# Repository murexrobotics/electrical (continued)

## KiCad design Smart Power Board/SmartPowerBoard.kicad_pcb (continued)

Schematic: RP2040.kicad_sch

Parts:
C11, C12, C13, C15, C16, C36, C37, C38, C39, C40: 0.1uF; C_0402_1005Metric
C14, C35: 1uF; C_0402_1005Metric
C33, C34: 10pF; C_0402_1005Metric
J2: USB_C_Receptacle_USB2.0_16P; USB_C_Receptacle_GCT_USB4105-xx-A_16P_TopMnt_Horizontal
R10, R11: 5.1k; R_0402_1005Metric
R19: 50; R_0402_1005Metric
R20, R21, R34, R35, R37, R38, R39: 10k; R_0402_1005Metric
R40, R41: 27; R_0402_1005Metric
SW1, SW2: SW_Push; SW_Push_SPST_NO_Alps_SKRK
U6: RP2040; QFN-56-1EP_7x7mm_P0.4mm_EP3.2x3.2mm_ThermalVias
U7: W25Q32JVSS; SOIC-8_5.23x5.23mm_P1.27mm
Y1: FL1200138; XTAL_FL1200138; PARTREV N/A

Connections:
/Buck Converter 3.3V/EN: U6.4 (GPIO2); also elsewhere on the board
/Buck Converter 5V/5V_{OUT}: J2.A4 (VBUS), J2.A9 (VBUS), J2.B4 (VBUS), J2.B9 (VBUS); also elsewhere on the board
/Buck Converter 5V/EN: U6.5 (GPIO3); also elsewhere on the board
/MCU/1.1V: C11.2, C12.2, U6.23 (DVDD), U6.45 (VREG_VOUT), U6.50 (DVDD); also elsewhere on the board
/MCU/3.3V_{CC}: C13.2, C14.2, C15.2, C16.2, C35.2, C36.2, C37.2, C38.2, C39.2, C40.2, R21.2, R34.1, R35.1, R37.1, R38.1, R39.1, U6.1 (IOVDD), U6.10 (IOVDD), U6.22 (IOVDD), U6.33 (IOVDD), U6.42 (IOVDD), U6.43 (ADC_AVDD), U6.44 (VREG_IN), U6.48 (USB_VDD), U6.49 (IOVDD), U7.8 (VCC); also elsewhere on the board
/MCU/CRIT: R34.2, U6.16 (GPIO13); also elsewhere on the board
/MCU/GPIO15: U6.18 (GPIO15); also elsewhere on the board
/MCU/QSPI_CS: R20.2, R21.1, U6.56 (QSPI_SS), U7.1 (~CS)
/MCU/QSPI_SCLK: U6.52 (QSPI_SCLK), U7.6 (CLK)
/MCU/QSPI_SD0: U6.53 (QSPI_SD0), U7.5 (DI(IO0))
/MCU/QSPI_SD1: U6.55 (QSPI_SD1), U7.2 (DO(IO1))
/MCU/QSPI_SD2: U6.54 (QSPI_SD2), U7.3 (IO2)
/MCU/QSPI_SD3: U6.51 (QSPI_SD3), U7.7 (IO3)
/MCU/RUN: R39.2, SW1.1, U6.26 (RUN)
/MCU/SCL: R37.2, U6.2 (GPIO0); also elsewhere on the board
/MCU/SDA: R38.2, U6.3 (GPIO1); also elsewhere on the board
/MCU/USB_BOOT: R20.1, SW2.1
/MCU/USB_M: J2.A6 (D+), J2.B6 (D+), R41.1
/MCU/USB_P: J2.A7 (D-), J2.B7 (D-), R40.1
/MCU/WARN: R35.2, U6.17 (GPIO14); also elsewhere on the board
/MCU/XIN: C34.1, U6.20 (XIN), Y1.1
/MCU/XOUT: R19.2, U6.21 (XOUT)
GND: C11.1, C12.1, C13.1, C14.1, C15.1, C16.1, C33.2, C34.2, C35.1, C36.1, C37.1, C38.1, C39.1, C40.1, J2.A1 (GND), J2.A12 (GND), J2.B1 (GND), J2.B12 (GND), J2.S1 (SHIELD), R10.2, R11.1, SW1.2, SW2.2, U6.19 (TESTEN), U6.57 (GND), U7.4 (GND), Y1.2 (GND), Y1.4 (GND__1); also elsewhere on the board
unnamed: C33.1, R19.1, Y1.3
unnamed: J2.A5 (CC1), R10.1
unnamed: J2.B5 (CC2), R11.2
unnamed: R41.2, U6.46 (USB_DM)
unnamed: R40.2, U6.47 (USB_DP)

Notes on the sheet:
RESET Button
USB_BOOT Button
USB Connection
Decoupling Capacitors
Clock
Flash Memory
RP2040 Main

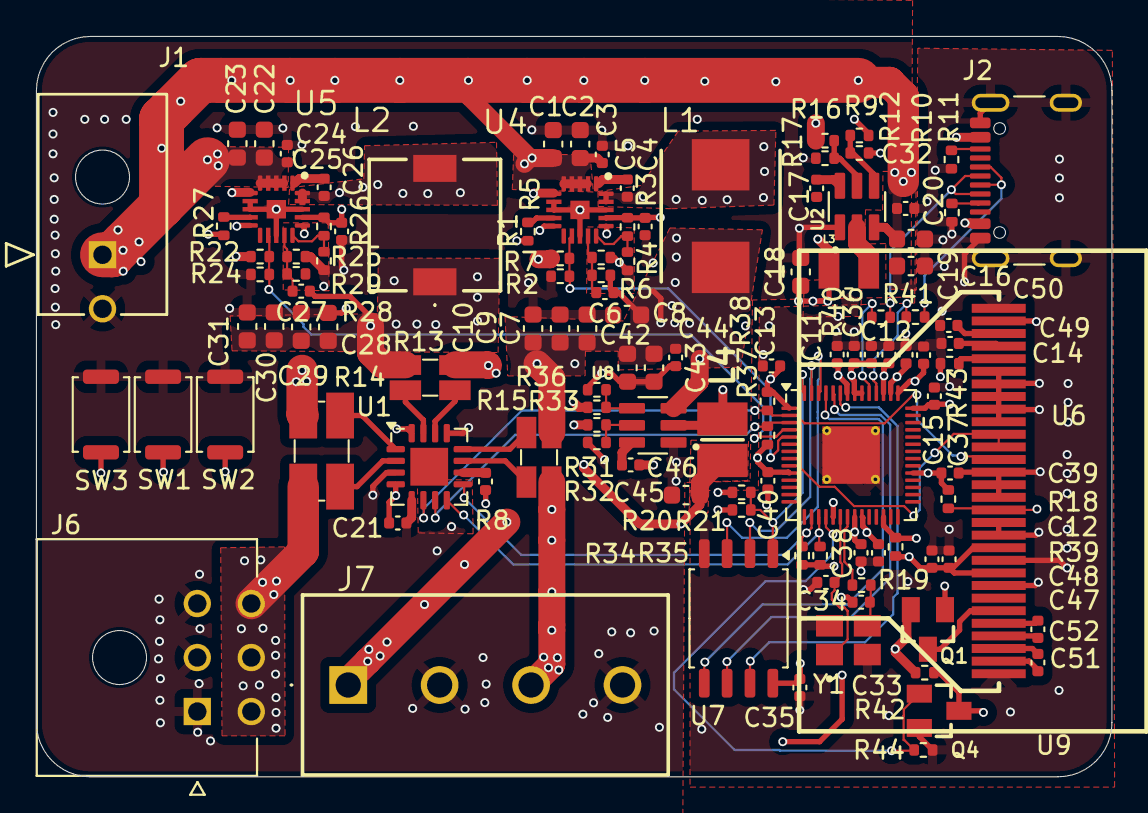
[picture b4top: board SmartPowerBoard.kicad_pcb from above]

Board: 4 copper layers, 59.8 x 41.1 mm, 116 parts (0 on the bottom side), 71 nets.

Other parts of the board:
C12#2: 0.1uF; C_0402_1005Metric

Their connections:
/MCU/1.1V: C12#2.2; also elsewhere on the board
GND: C12#2.1; also elsewhere on the board

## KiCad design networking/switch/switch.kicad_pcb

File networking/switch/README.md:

# Documentation

<https://docs.murexrobotics.com/elec/boards/networking/switch>

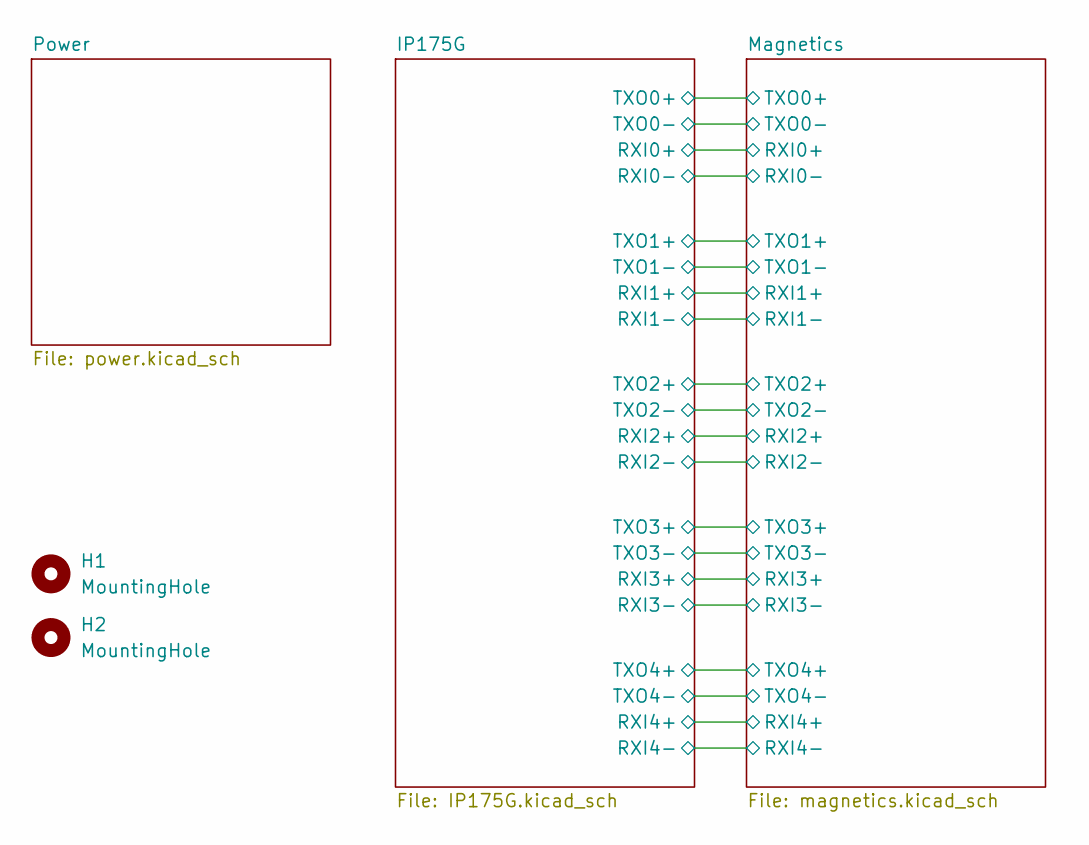
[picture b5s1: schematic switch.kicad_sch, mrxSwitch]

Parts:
H1, H2: MountingHole; MountingHole_3.2mm_M3

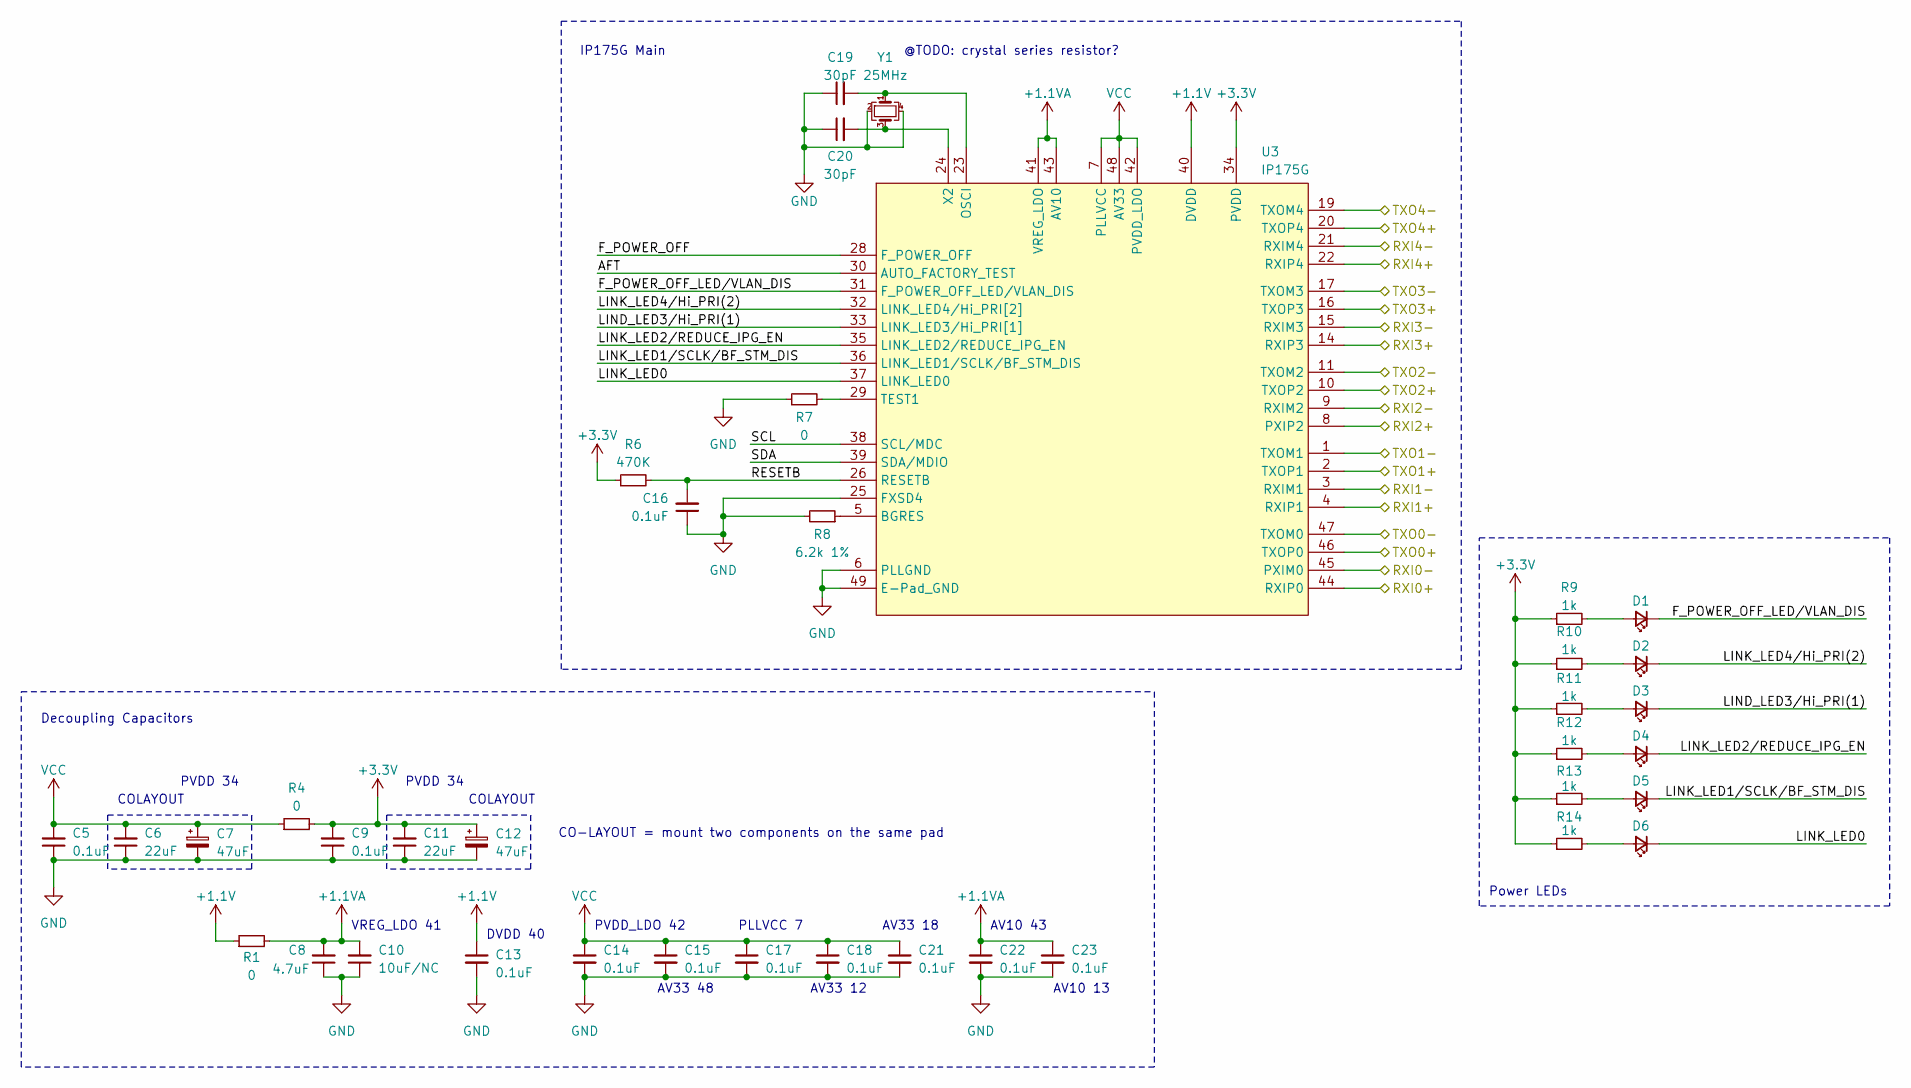
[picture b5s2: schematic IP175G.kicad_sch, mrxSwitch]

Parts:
C5, C9, C13, C14, C15, C16, C17, C18, C21, C22, C23: 0.1uF; C_0402_1005Metric
C6, C11: 22uF; C_0402_1005Metric
C7, C12: 47uF; C_0402_1005Metric
C8: 4.7uF; C_0402_1005Metric
C10: 10uF/NC; C_0402_1005Metric
C19, C20: 30pF; C_0603_1608Metric
D1, D2, D3, D4, D5, D6: LED_0603_1608Metric
R1, R4, R7: 0; R_0402_1005Metric
R6: 470K; R_0402_1005Metric
R8: 6.2k 1%; R_0402_1005Metric
R9, R10, R11, R12, R13, R14: 1k; R_0402_1005Metric
U3: IP175G; QFN-48-1EP_6x6mm_P0.4mm_EP4.3x4.3mm_ThermalVias
Y1: 25MHz; Crystal_SMD_3225-4Pin_3.2x2.5mm

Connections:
+1.1V: C13.1, R1.1, U3.27 (DVDD), U3.40 (DVDD)
+1.1VA: C8.2, C10.2, C22.1, C23.1, R1.2, U3.13 (AV10), U3.41 (VREG_LDO), U3.43 (AV10)
+3.3V: C9.2, C11.2, C12.1, R4.2, R6.1, R9.1, R10.1, R11.1, R12.1, R13.1, R14.1, U3.34 (PVDD)
/IP175G/AFT: U3.30 (AUTO_FACTORY_TEST)
/IP175G/F_POWER_OFF: U3.28 (F_POWER_OFF)
/IP175G/F_POWER_OFF_LED/VLAN_DIS: D1.1 (K), U3.31 (F_POWER_OFF_LED/VLAN_DIS)
/IP175G/LIND_LED3/Hi_PRI(1): D3.1 (K), U3.33 (LINK_LED3/Hi_PRI[1])
/IP175G/LINK_LED0: D6.1 (K), U3.37 (LINK_LED0)
/IP175G/LINK_LED1/SCLK/BF_STM_DIS: D5.1 (K), U3.36 (LINK_LED1/SCLK/BF_STM_DIS)
/IP175G/LINK_LED2/REDUCE_IPG_EN: D4.1 (K), U3.35 (LINK_LED2/REDUCE_IPG_EN)
/IP175G/LINK_LED4/Hi_PRI(2): D2.1 (K), U3.32 (LINK_LED4/Hi_PRI[2])
/IP175G/RESETB: C16.2, R6.2, U3.26 (RESETB)
/IP175G/RXI0+: U3.44 (RXIP0); also elsewhere on the board
/IP175G/RXI0-: U3.45 (PXIM0); also elsewhere on the board
/IP175G/RXI1+: U3.4 (RXIP1); also elsewhere on the board
/IP175G/RXI1-: U3.3 (RXIM1); also elsewhere on the board
/IP175G/RXI2+: U3.8 (PXIP2); also elsewhere on the board
/IP175G/RXI2-: U3.9 (RXIM2); also elsewhere on the board
/IP175G/RXI3+: U3.14 (RXIP3); also elsewhere on the board
/IP175G/RXI3-: U3.15 (RXIM3); also elsewhere on the board
/IP175G/RXI4+: U3.22 (RXIP4); also elsewhere on the board
/IP175G/RXI4-: U3.21 (RXIM4); also elsewhere on the board
/IP175G/SCL: U3.38 (SCL/MDC)
/IP175G/SDA: U3.39 (SDA/MDIO)
/IP175G/TXO0+: U3.46 (TXOP0); also elsewhere on the board
/IP175G/TXO0-: U3.47 (TXOM0); also elsewhere on the board
/IP175G/TXO1+: U3.2 (TXOP1); also elsewhere on the board
/IP175G/TXO1-: U3.1 (TXOM1); also elsewhere on the board
/IP175G/TXO2+: U3.10 (TXOP2); also elsewhere on the board
/IP175G/TXO2-: U3.11 (TXOM2); also elsewhere on the board
/IP175G/TXO3+: U3.16 (TXOP3); also elsewhere on the board
/IP175G/TXO3-: U3.17 (TXOM3); also elsewhere on the board
/IP175G/TXO4+: U3.20 (TXOP4); also elsewhere on the board
/IP175G/TXO4-: U3.19 (TXOM4); also elsewhere on the board
GND: C5.1, C6.1, C7.2, C8.1, C9.1, C10.1, C11.1, C12.2, C13.2, C14.2, C15.2, C16.1, C17.2, C18.2, C19.1, C20.1, C21.2, C22.2, C23.2, R7.1, R8.2, U3.6 (PLLGND), U3.25 (FXSD4), U3.49 (E-Pad_GND), Y1.2, Y1.4; also elsewhere on the board
unnamed: D1.2 (A), R9.2
unnamed: D2.2 (A), R10.2
unnamed: D3.2 (A), R11.2
unnamed: D4.2 (A), R12.2
unnamed: D5.2 (A), R13.2
unnamed: D6.2 (A), R14.2
unnamed: R8.1, U3.5 (BGRES)
unnamed: C19.2, U3.23 (OSCI), Y1.1
unnamed: R7.2, U3.29 (TEST1)
unnamed: C20.2, U3.24 (X2), Y1.3
VCC: C5.2, C6.2, C7.1, C14.1, C15.1, C17.1, C18.1, C21.1, R4.1, U3.7 (PLLVCC), U3.12 (AV33), U3.18 (AV33), U3.42 (PVDD_LDO), U3.48 (AV33); also elsewhere on the board

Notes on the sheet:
AV33 12
PVDD 34
PLLVCC 7
Decoupling Capacitors
DVDD 40
Power LEDs
VREG_LDO 41
AV33 18
PVDD_LDO 42
AV10 43
AV33 48
CO-LAYOUT = mount two components on the same pad
@TODO: crystal series resistor?
COLAYOUT
IP175G Main
AV10 13

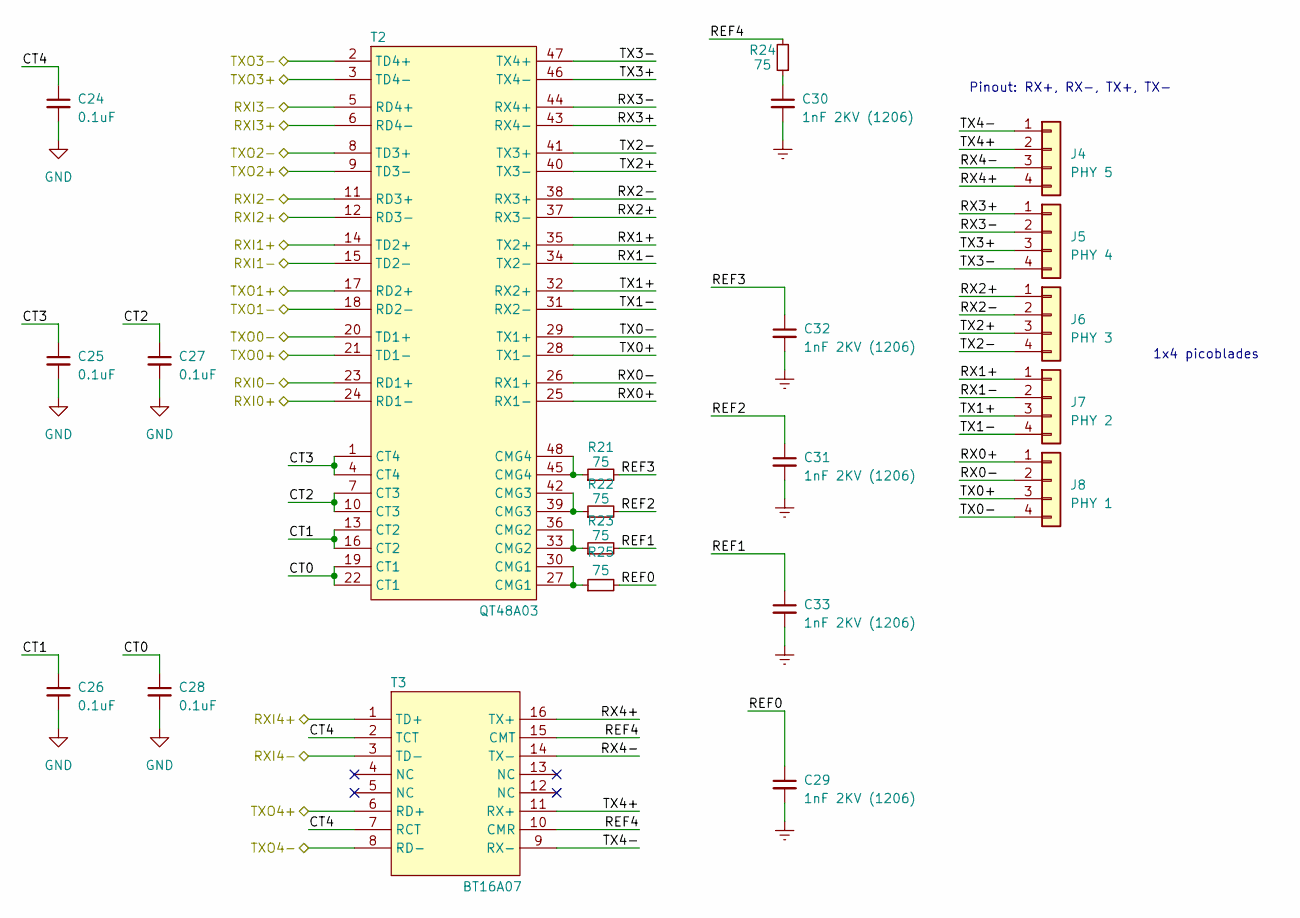
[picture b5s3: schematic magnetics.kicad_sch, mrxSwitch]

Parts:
C24, C25, C26, C27, C28: 0.1uF; C_0402_1005Metric
C29, C30, C31, C32, C33: 1nF 2KV (1206); C_1206_3216Metric
J4: PHY 5; Molex_PicoBlade_53047-0410_1x04_P1.25mm_Vertical
J5: PHY 4; Molex_PicoBlade_53047-0410_1x04_P1.25mm_Vertical
J6: PHY 3; Molex_PicoBlade_53047-0410_1x04_P1.25mm_Vertical
J7: PHY 2; Molex_PicoBlade_53047-0410_1x04_P1.25mm_Vertical
J8: PHY 1; Molex_PicoBlade_53047-0410_1x04_P1.25mm_Vertical
R21, R22, R23, R24, R25: 75; R_0402_1005Metric
T2: QT48A03
T3: BT16A07

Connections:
/IP175G/RXI0+: T2.24 (RD1-); also elsewhere on the board
/IP175G/RXI0-: T2.23 (RD1+); also elsewhere on the board
/IP175G/RXI1+: T2.14 (TD2+); also elsewhere on the board
/IP175G/RXI1-: T2.15 (TD2-); also elsewhere on the board
/IP175G/RXI2+: T2.12 (RD3-); also elsewhere on the board
/IP175G/RXI2-: T2.11 (RD3+); also elsewhere on the board
/IP175G/RXI3+: T2.6 (RD4-); also elsewhere on the board
/IP175G/RXI3-: T2.5 (RD4+); also elsewhere on the board
/IP175G/RXI4+: T3.1 (TD+); also elsewhere on the board
/IP175G/RXI4-: T3.3 (TD-); also elsewhere on the board
/IP175G/TXO0+: T2.21 (TD1-); also elsewhere on the board
/IP175G/TXO0-: T2.20 (TD1+); also elsewhere on the board
/IP175G/TXO1+: T2.17 (RD2+); also elsewhere on the board
/IP175G/TXO1-: T2.18 (RD2-); also elsewhere on the board
/IP175G/TXO2+: T2.9 (TD3-); also elsewhere on the board
/IP175G/TXO2-: T2.8 (TD3+); also elsewhere on the board
/IP175G/TXO3+: T2.3 (TD4-); also elsewhere on the board
/IP175G/TXO3-: T2.2 (TD4+); also elsewhere on the board
/IP175G/TXO4+: T3.6 (RD+); also elsewhere on the board
/IP175G/TXO4-: T3.8 (RD-); also elsewhere on the board
/Magnetics/CT0: C28.1, T2.19 (CT1), T2.22 (CT1)
/Magnetics/CT1: C26.1, T2.13 (CT2), T2.16 (CT2)
/Magnetics/CT2: C27.1, T2.7 (CT3), T2.10 (CT3)
/Magnetics/CT3: C25.1, T2.1 (CT4), T2.4 (CT4)
/Magnetics/CT4: C24.1, T3.2 (TCT), T3.7 (RCT)
/Magnetics/REF0: C29.1, R25.2
/Magnetics/REF1: C33.1, R23.2
/Magnetics/REF2: C31.1, R22.2
/Magnetics/REF3: C32.1, R21.2
/Magnetics/REF4: R24.2, T3.10 (CMR), T3.15 (CMT)
/Magnetics/RX0+: J8.1, T2.25 (RX1-)
/Magnetics/RX0-: J8.2, T2.26 (RX1+)
/Magnetics/RX1+: J7.1, T2.35 (TX2+)
/Magnetics/RX1-: J7.2, T2.34 (TX2-)
/Magnetics/RX2+: J6.1, T2.37 (RX3-)
/Magnetics/RX2-: J6.2, T2.38 (RX3+)
/Magnetics/RX3+: J5.1, T2.43 (RX4-)
/Magnetics/RX3-: J5.2, T2.44 (RX4+)
/Magnetics/RX4+: J4.4, T3.16 (TX+)
/Magnetics/RX4-: J4.3, T3.14 (TX-)
/Magnetics/TX0+: J8.3, T2.28 (TX1-)
/Magnetics/TX0-: J8.4, T2.29 (TX1+)
/Magnetics/TX1+: J7.3, T2.32 (RX2+)
/Magnetics/TX1-: J7.4, T2.31 (RX2-)
/Magnetics/TX2+: J6.3, T2.40 (TX3-)
/Magnetics/TX2-: J6.4, T2.41 (TX3+)
/Magnetics/TX3+: J5.3, T2.46 (TX4-)
/Magnetics/TX3-: J5.4, T2.47 (TX4+)
/Magnetics/TX4+: J4.2, T3.11 (RX+)
/Magnetics/TX4-: J4.1, T3.9 (RX-)
Earth: C29.2, C30.2, C31.2, C32.2, C33.2
GND: C24.2, C25.2, C26.2, C27.2, C28.2; also elsewhere on the board
unnamed: C30.1, R24.1
unnamed: R21.1, T2.45 (CMG4), T2.48 (CMG4)
unnamed: R22.1, T2.39 (CMG3), T2.42 (CMG3)
unnamed: R23.1, T2.33 (CMG2), T2.36 (CMG2)
unnamed: R25.1, T2.27 (CMG1), T2.30 (CMG1)

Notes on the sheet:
Pinout: RX+, RX-, TX+, TX-
1x4 picoblades

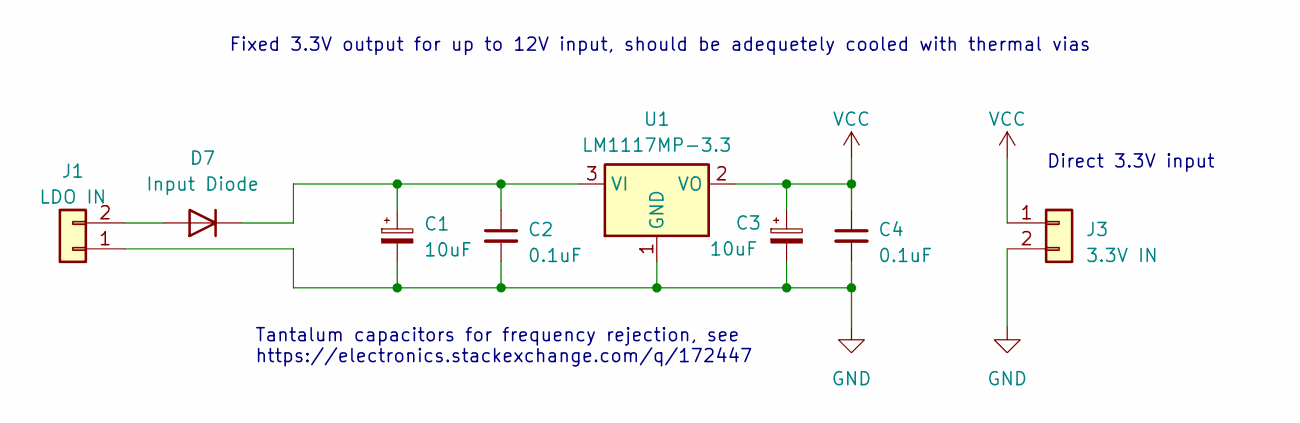
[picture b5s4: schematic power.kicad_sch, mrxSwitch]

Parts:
C1, C3: 10uF; CP_EIA-3216-18_Kemet-A
C2, C4: 0.1uF; C_0402_1005Metric
D7: Input Diode; D_SMA
J1: LDO IN; Molex_PicoBlade_53047-0210_1x02_P1.25mm_Vertical
J3: 3.3V IN; Molex_PicoBlade_53047-0210_1x02_P1.25mm_Vertical
U1: LM1117MP-3.3; SOT-223-3_TabPin2

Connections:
GND: C1.2, C2.2, C3.2, C4.2, J1.1, J3.2, U1.1 (GND); also elsewhere on the board
unnamed: D7.2 (A), J1.2
unnamed: C1.1, C2.1, D7.1 (K), U1.3 (VI)
VCC: C3.1, C4.1, J3.1, U1.2 (VO); also elsewhere on the board

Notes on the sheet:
Direct 3.3V input
Tantalum capacitors for frequency rejection, see https://electronics.stackexchange.com/q/172447
Fixed 3.3V output for up to 12V input, should be adequetely cooled with thermal vias

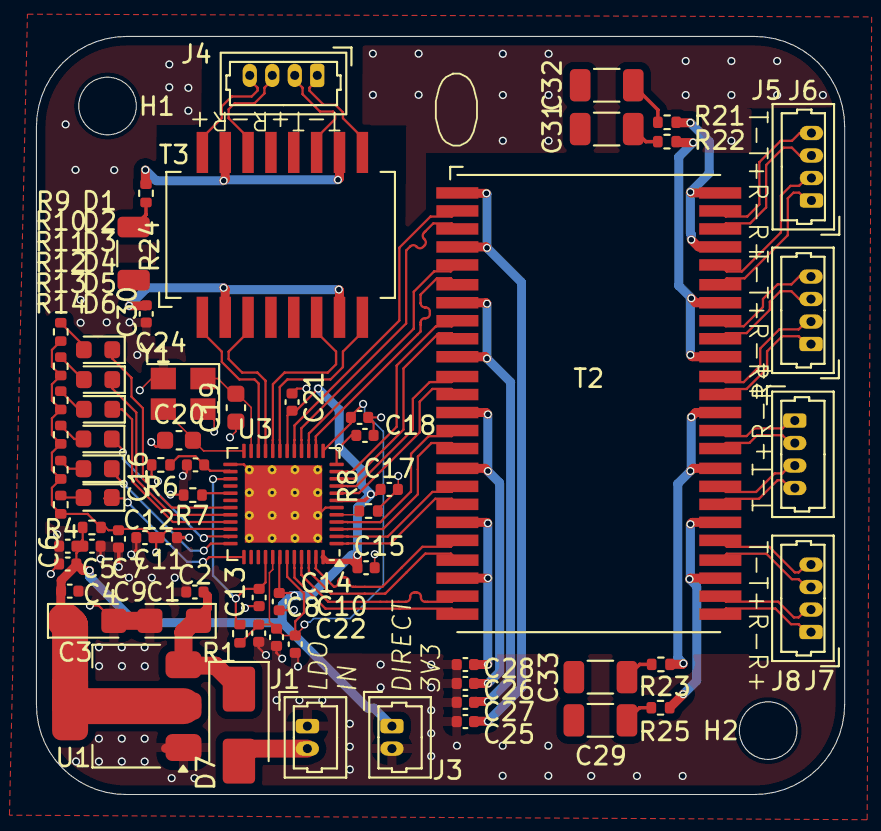
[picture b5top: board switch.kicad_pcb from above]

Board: 4 copper layers, 44.9 x 42.1 mm, 70 parts (0 on the bottom side), 80 nets.

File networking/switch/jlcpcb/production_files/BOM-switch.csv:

Comment,Designator,Footprint,LCSC,Quantity
22uF,"C11,C12,C6,C7",C_0402_1005Metric,C105226,4
1k,"R10,R11,R12,R13,R14,R9",R_0402_1005Metric,C11702,6
0.1uF,"C13,C14,C15,C16,C17,C18,C2,C21,C22,C23,C24,C25,C26,C27,C28,C4,C5,C9",C_0402_1005Metric,C1525,18
10uF/NC,C10,C_0402_1005Metric,C15525,1
30pF,"C19,C20",C_0603_1608Metric,C1658,2
0,"R1,R4,R7",R_0402_1005Metric,C17168,3
BT16A07,T3,BT16A07,C216355,1
QT48A03,T2,QT48A03,C216365,1
~,"D3,D6",LED_0603_1608Metric,C2286,2
~,"D2,D5",LED_0603_1608Metric,C2290,2
4.7uF,C8,C_0402_1005Metric,C23733,1
Input Diode,D7,D_SMA,C2479,1
75,"R21,R22,R23,R24,R25",R_0402_1005Metric,C25133,5
470K,R6,R_0402_1005Metric,C25562,1
6.2k 1%,R8,R_0402_1005Metric,C25915,1
25MHz,Y1,Crystal_SMD_3225-4Pin_3.2x2.5mm,C337588,1
LM1117MP-3.3,U1,SOT-223-3_TabPin2,C498153,1
10uF,"C1,C3",CP_EIA-3216-18_Kemet-A,C7171,2
~,"D1,D4",LED_0603_1608Metric,C72038,2
IP175G,U3,QFN-48-1EP_6x6mm_P0.4mm_EP4.3x4.3mm_ThermalVias,C80220,1
1nF 2KV (1206),"C29,C30,C31,C32,C33",C_1206_3216Metric,C9196,5
PHY 1,J8,Molex_PicoBlade_53047-0410_1x04_P1.25mm_Vertical,,1
PHY 3,J6,Molex_PicoBlade_53047-0410_1x04_P1.25mm_Vertical,,1
MountingHole,H1,MountingHole_3.2mm_M3,,1
PHY 5,J4,Molex_PicoBlade_53047-0410_1x04_P1.25mm_Vertical,,1
MountingHole,H2,MountingHole_3.2mm_M3,,1
LDO IN,J1,Molex_PicoBlade_53047-0210_1x02_P1.25mm_Vertical,,1
PHY 2,J7,Molex_PicoBlade_53047-0410_1x04_P1.25mm_Vertical,,1
3.3V IN,J3,Molex_PicoBlade_53047-0210_1x02_P1.25mm_Vertical,,1
PHY 4,J5,Molex_PicoBlade_53047-0410_1x04_P1.25mm_Vertical,,1

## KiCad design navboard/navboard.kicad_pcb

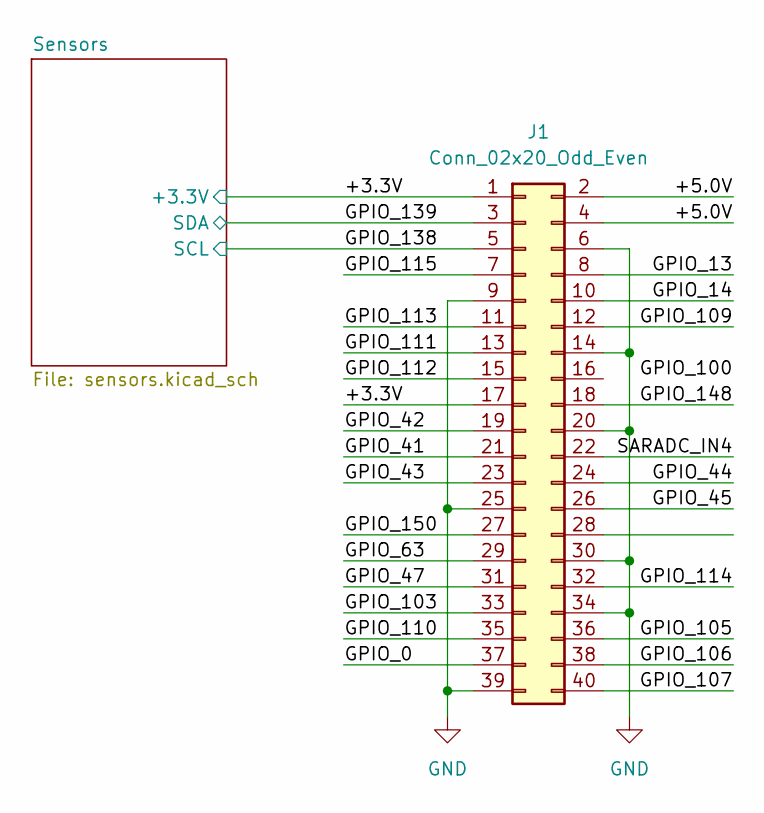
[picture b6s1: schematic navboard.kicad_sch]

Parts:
J1: Conn_02x20_Odd_Even; PinSocket_2x20_P2.54mm_Vertical

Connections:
/+3.3V: J1.1, J1.17; also elsewhere on the board
/+5.0V: J1.2, J1.4
/GPIO_0: J1.37
/GPIO_13: J1.8
/GPIO_14: J1.10
/GPIO_41: J1.21
/GPIO_42: J1.19
/GPIO_43: J1.23
/GPIO_44: J1.24
/GPIO_45: J1.26
/GPIO_47: J1.31
/GPIO_63: J1.29
/GPIO_103: J1.33
/GPIO_105: J1.36
/GPIO_106: J1.38
/GPIO_107: J1.40
/GPIO_109: J1.12
/GPIO_110: J1.35
/GPIO_111: J1.13
/GPIO_112: J1.15
/GPIO_113: J1.11
/GPIO_114: J1.32
/GPIO_115: J1.7
/GPIO_138: J1.5; also elsewhere on the board
/GPIO_139: J1.3; also elsewhere on the board
/GPIO_148: J1.18
/GPIO_150: J1.27
/SARADC_IN4: J1.22
GND: J1.6, J1.9, J1.14, J1.20, J1.25, J1.30, J1.34, J1.39; also elsewhere on the board

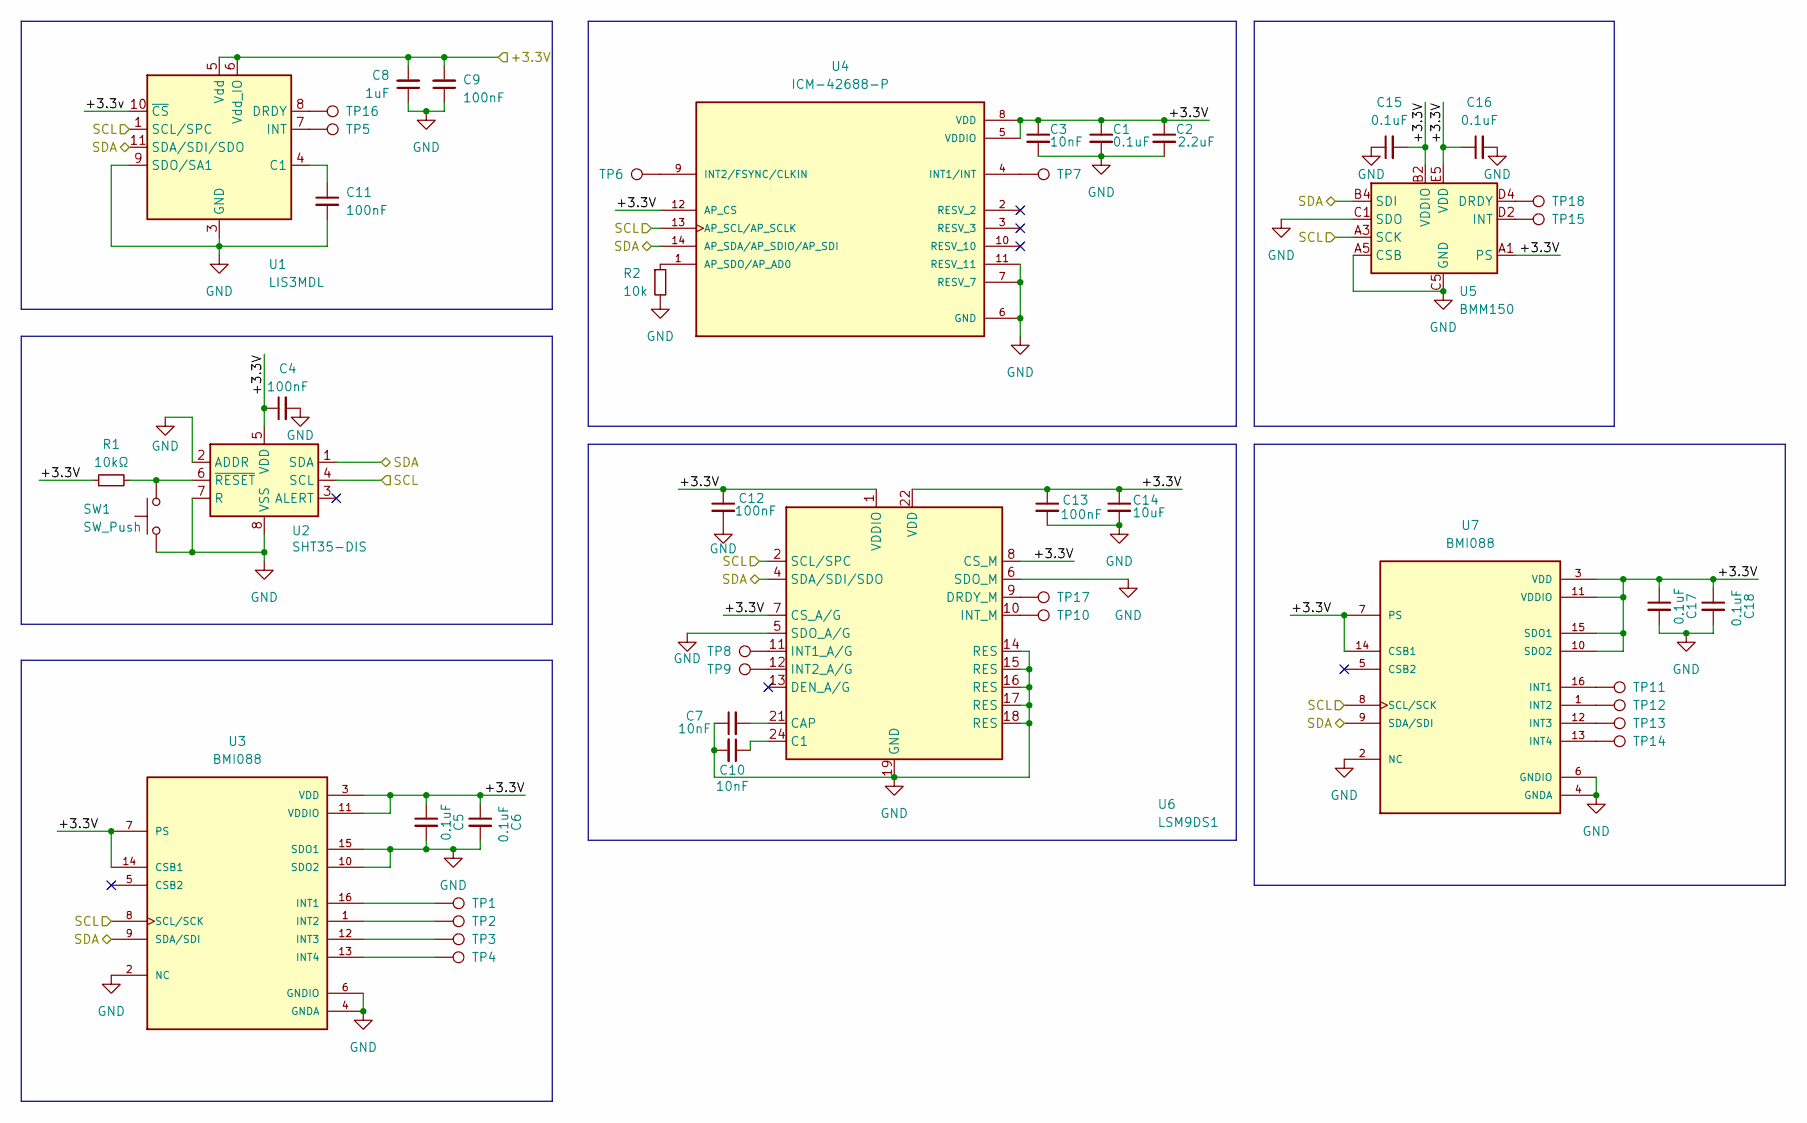
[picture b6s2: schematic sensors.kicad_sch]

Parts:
C1, C5, C6, C15, C16, C17, C18: 0.1uF; C_0603_1608Metric
C2: 2.2uF; C_0603_1608Metric
C3, C7, C10: 10nF; C_0603_1608Metric
C4, C9, C11, C12, C13: 100nF; C_0603_1608Metric
C8: 1uF; C_0603_1608Metric
C14: 10uF; C_0603_1608Metric
R1: 10kΩ; R_0603_1608Metric
R2: 10k; R_0603_1608Metric
SW1: SW_Push; SW_Push_SPST_NO_Alps_SKRK
TP1, TP2, TP3, TP4, TP5, TP6, TP7, TP8, TP9, TP10, TP11, TP12, TP13, TP14, TP15, TP16, TP17, TP18: TestPoint; TestPoint_Pad_D1.0mm
U1: LIS3MDL; LGA-12_2x2mm_P0.5mm
U2: SHT35-DIS; Sensirion_DFN-8-1EP_2.5x2.5mm_P0.5mm_EP1.1x1.7mm
U3, U7: BMI088; PQFN50P450X300X100-16N
U4: ICM-42688-P; LGA14_2P5X3X0P91_IVS; PARTREV 1.2
U5: BMM150; WLCSP-12_1.56x1.56mm_P0.4mm
U6: LSM9DS1; LGA-24L_3x3.5mm_P0.43mm

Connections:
/+3.3V: C1.1, C2.1, C3.1, C4.1, C5.1, C6.1, C8.2, C9.2, C12.1, C13.1, C14.1, C15.2, C16.1, C17.1, C18.1, R1.1, U1.5 (Vdd), U1.6 (Vdd_IO), U2.5 (VDD), U3.3 (VDD), U3.7 (PS), U3.11 (VDDIO), U3.14 (CSB1), U4.5 (VDDIO), U4.8 (VDD), U4.12 (AP_CS), U5.A1 (PS), U5.B2 (VDDIO), U5.E5 (VDD), U6.1 (VDDIO), U6.3 (VDDIO), U6.7 (CS_A/G), U6.8 (CS_M), U6.22 (VDD), U6.23 (VDD), U7.3 (VDD), U7.7 (PS), U7.10 (SDO2), U7.11 (VDDIO), U7.14 (CSB1), U7.15 (SDO1); also elsewhere on the board
/GPIO_138: U1.1 (SCL/SPC), U2.4 (SCL), U3.8 (SCL/SCK), U4.13 (AP_SCL/AP_SCLK), U5.A3 (SCK), U6.2 (SCL/SPC), U7.8 (SCL/SCK); also elsewhere on the board
/GPIO_139: U1.11 (SDA/SDI/SDO), U2.1 (SDA), U3.9 (SDA/SDI), U4.14 (AP_SDA/AP_SDIO/AP_SDI), U5.B4 (SDI), U6.4 (SDA/SDI/SDO), U7.9 (SDA/SDI); also elsewhere on the board
/Sensors/+3.3v: U1.10 (~CS)
GND: C1.2, C2.2, C3.2, C4.2, C5.2, C6.2, C7.1, C8.1, C9.1, C10.2, C11.2, C12.2, C13.2, C14.2, C15.1, C16.2, C17.2, C18.2, R2.2, SW1.1, U1.2 (GND), U1.3 (GND), U1.9 (SDO/SA1), U1.12 (GND), U2.2 (ADDR), U2.7 (R), U2.8 (VSS), U2.9 (VSS), U3.2 (NC), U3.4 (GNDA), U3.6 (GNDIO), U3.10 (SDO2), U3.15 (SDO1), U4.6 (GND), U4.7 (RESV_7), U4.11 (RESV_11), U5.A5 (CSB), U5.C1 (SDO), U5.C5 (GND), U5.E1 (GND), U5.E3 (GND), U6.5 (SDO_A/G), U6.6 (SDO_M), U6.14 (RES), U6.15 (RES), U6.16 (RES), U6.17 (RES), U6.18 (RES), U6.19 (GND), U6.20 (GND), U7.2 (NC), U7.4 (GNDA), U7.6 (GNDIO); also elsewhere on the board
unnamed: C11.1, U1.4 (C1)
unnamed: TP16.1, U1.8 (DRDY)
unnamed: TP5.1, U1.7 (INT)
unnamed: R1.2, SW1.2, U2.6 (~RESET)
unnamed: TP1.1, U3.16 (INT1)
unnamed: TP2.1, U3.1 (INT2)
unnamed: TP3.1, U3.12 (INT3)
unnamed: TP4.1, U3.13 (INT4)
unnamed: R2.1, U4.1 (AP_SDO/AP_AD0)
unnamed: TP7.1, U4.4 (INT1/INT)
unnamed: TP6.1, U4.9 (INT2/FSYNC/CLKIN)
unnamed: TP18.1, U5.D4 (DRDY)
unnamed: TP15.1, U5.D2 (INT)
unnamed: C10.1, U6.24 (C1)
unnamed: C7.2, U6.21 (CAP)
unnamed: TP17.1, U6.9 (DRDY_M)
unnamed: TP8.1, U6.11 (INT1_A/G)
unnamed: TP9.1, U6.12 (INT2_A/G)
unnamed: TP10.1, U6.10 (INT_M)
unnamed: TP11.1, U7.16 (INT1)
unnamed: TP12.1, U7.1 (INT2)
unnamed: TP13.1, U7.12 (INT3)
unnamed: TP14.1, U7.13 (INT4)

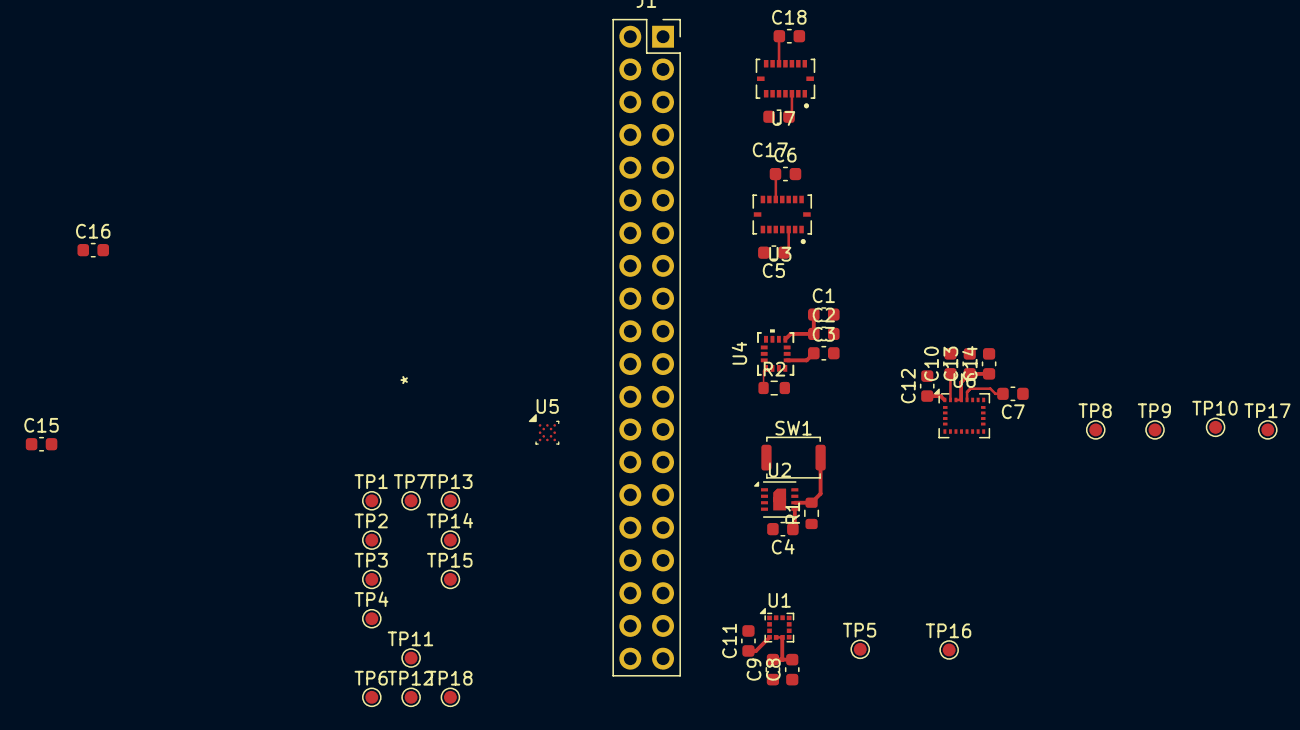
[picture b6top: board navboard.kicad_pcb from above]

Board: 2 copper layers, 47 parts (0 on the bottom side), 28 nets.

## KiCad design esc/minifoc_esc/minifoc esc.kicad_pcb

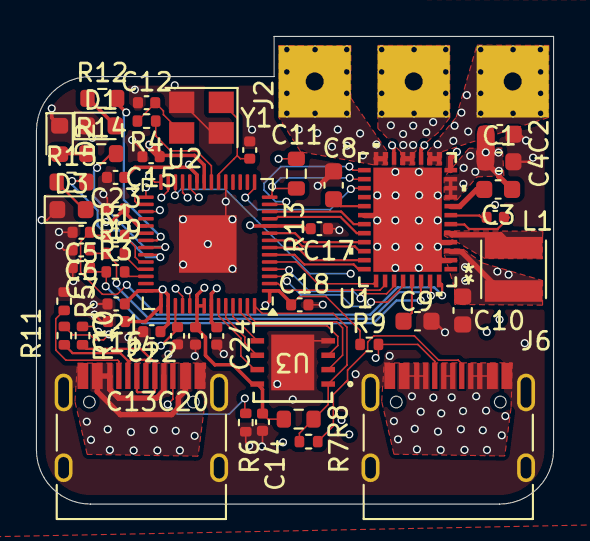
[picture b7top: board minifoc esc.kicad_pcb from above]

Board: 4 copper layers, 28.7 x 26.0 mm, 50 parts (0 on the bottom side), 55 nets.

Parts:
C1: 0.1uF; C_0603_1608Metric
C2: 10uF; C_0603_1608Metric
C3, C8, C9: 1uF; C_0603_1608Metric
C4: 47nF; C_0402_1005Metric
C5, C6, C7: 30pF; C_0402_1005Metric
C10: 22uF; C_0603_1608Metric
C11, C12: 27pF; C_0402_1005Metric
C13, C14, C21, C22: 1uF; C_0402_1005Metric
C15, C16, C17, C18, C19, C20, C23, C24: 0.1uF; C_0402_1005Metric
D1, D2, D3: LED_Small; LED_0603_1608Metric
J2: Conn_01x03; ESC
J4, J6: USB_C_Receptacle_USB2.0_16P; USB_C_Receptacle_HRO_TYPE-C-31-M-12
L1: 47uH; SMNR3012-470MT
R1, R2, R3, R4, R7, R9: 1k; R_0402_1005Metric
R5, R6: 5.1k; R_0402_1005Metric
R8, R13: 10k; R_0603_1608Metric
R10, R11: 27; R_0402_1005Metric
R12, R14, R15: 2.7k; R_0603_1608Metric
U1: DRV8316CRRGFR; VQFN40_RGF_TEX-L
U2: RP2040; QFN-56-1EP_7x7mm_P0.4mm_EP3.2x3.2mm
U3: W25Q64JVXGIQ TR; DFN_XGIQ TR_WIN
Y1: 12Mhz; Crystal_SMD_3225-4Pin_3.2x2.5mm

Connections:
/AVDD: C8.1, U1.25 (AVDD)
/CP: C3.2, U1.8 (CP)
/CPH: C4.1, U1.7 (CPH)
/CPL: C4.2, U1.6 (CPL)
/DRVOFF: U1.21 (DRVOFF), U2.13 (GPIO10)
/FB_BK: C10.1, C14.1, C15.1, C16.1, C17.1, C18.1, C19.1, C20.1, C21.1, C22.1, L1.2, R8.2, R9.2, R13.2, U1.3 (FB_BK), U2.1 (IOVDD), U2.10 (IOVDD), U2.22 (IOVDD), U2.33 (IOVDD), U2.42 (IOVDD), U2.43 (ADC_AVDD), U2.44 (VREG_IN), U2.48 (USB_VDD), U2.49 (IOVDD), U3.8 (VCC)
/INHA: U1.27 (INHA), U2.12 (GPIO9)
/INHB: U1.29 (INHB), U2.9 (GPIO7)
/INHC: U1.31 (INHC), U2.7 (GPIO5)
/INLA: U1.28 (INLA), U2.11 (GPIO8)
/INLB: U1.30 (INLB), U2.8 (GPIO6)
/INLC: U1.32 (INLC), U2.6 (GPIO4)
/NFAULT: R13.1, U1.22 (NFAULT), U2.14 (GPIO11)
/NSCS: U1.36 (NSCS), U2.3 (GPIO1)
/NSLEEP: U1.23 (NSLEEP), U2.15 (GPIO12)
/RP2040/+1.1V: C13.1, C23.1, C24.1, U2.23 (DVDD), U2.45 (VREG_VOUT), U2.50 (DVDD)
/RP2040/LED1: R15.2, U2.37 (GPIO25)
/RP2040/LED2: R14.2, U2.36 (GPIO24)
/RP2040/LED3: R12.2, U2.35 (GPIO23)
/RP2040/QSPI_CS: R7.1, R8.1, U2.56 (QSPI_SS), U3.1 (/CS)
/RP2040/QSPI_SCLK: U2.52 (QSPI_SCLK), U3.6 (CLK)
/RP2040/QSPI_SD0: U2.53 (QSPI_SD0), U3.5 (DI_(IO0))
/RP2040/QSPI_SD1: U2.55 (QSPI_SD1), U3.2 (DO_(IO1))
/RP2040/QSPI_SD2: U2.54 (QSPI_SD2), U3.3 (IO2)
/RP2040/QSPI_SD3: U2.51 (QSPI_SD3), U3.7 (IO3)
/RP2040/RUN: J6.B7 (D-), R9.1, U2.26 (RUN)
/RP2040/SA: R1.2, U2.38 (GPIO26_ADC0)
/RP2040/SB: R2.2, U2.39 (GPIO27_ADC1)
/RP2040/SC: R3.2, U2.40 (GPIO28_ADC2)
/RP2040/USB_BOOT: J6.B6 (D+), R7.2
/RP2040/USB_N: J4.A7 (D-), J4.B7 (D-), R11.1
/RP2040/USB_P: J4.A6 (D+), J4.B6 (D+), R10.2
/RP2040/XIN: C11.2, U2.20 (XIN), Y1.1
/RP2040/XOUT: R4.1, U2.21 (XOUT)
/SCLK: U1.35 (SCLK), U2.4 (GPIO2)
/SDI: U1.34 (SDI), U2.2 (GPIO0)
/SDO: U1.33 (SDO), U2.5 (GPIO3)
/SOA: C5.1, R1.1, U1.40 (SOA)
/SOB: C6.1, R2.1, U1.39 (SOB)
/SOC: C7.1, R3.1, U1.38 (SOC)
/SW_BK: L1.1, U1.5 (SW_BK)
/VREF/ILIM: C9.1, U1.37 (VREF/ILIM)
GND: C1.2, C2.2, C5.2, C6.2, C7.2, C8.2, C9.2, C10.2, C11.1, C12.1, C13.2, C14.2, C15.2, C16.2, C17.2, C18.2, C19.2, C20.2, C21.2, C22.2, C23.2, C24.2, D1.1 (K), D2.1 (K), D3.1 (K), J4.A1 (GND), J4.A12 (GND), J4.B1 (GND), J4.B12 (GND), J4.S1 (SHIELD), J6.A1 (GND), J6.A12 (GND), J6.B1 (GND), J6.B12 (GND), J6.S1 (SHIELD), R5.1, R6.1, U1.2 (AGND), U1.4 (GND_BK), U1.12 (PGND), U1.15 (PGND), U1.18 (PGND), U1.26 (AGND), U1.41 (EPAD), U2.19 (TESTEN), U2.57 (GND), U3.4 (GND), Y1.2, Y1.4
unnamed: C12.2, R4.2, Y1.3
unnamed: D1.2 (A), R12.1
unnamed: D2.2 (A), R14.1
unnamed: D3.2 (A), R15.1
unnamed: J4.A5 (CC1), R5.2
unnamed: J4.B5 (CC2), R6.2
unnamed: R11.2, U2.46 (USB_DM)
unnamed: R10.1, U2.47 (USB_DP)
OUTA: J2.1, U1.13 (OUTA), U1.14 (OUTA)
OUTB: J2.2, U1.16 (OUTB), U1.17 (OUTB)
OUTC: J2.3, U1.19 (OUTC), U1.20 (OUTC)
VCC: C1.1, C2.1, C3.1, J4.A4 (VBUS), J4.A8 (SBU1), J4.A9 (VBUS), J4.B4 (VBUS), J4.B8 (SBU2), J4.B9 (VBUS), J6.A4 (VBUS), J6.A5 (CC1), J6.A6 (D+), J6.A7 (D-), J6.A8 (SBU1), J6.A9 (VBUS), J6.B4 (VBUS), J6.B5 (CC2), J6.B8 (SBU2), J6.B9 (VBUS), U1.9 (VM), U1.10 (VM), U1.11 (VM)

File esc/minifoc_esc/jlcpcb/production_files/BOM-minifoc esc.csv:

Comment,Designator,Footprint,LCSC
1k,"R1,R2,R3,R4,R7,R9",R_0402_1005Metric,C11702
2.7k,"R12,R14,R15",R_0603_1608Metric,C13167
47uH,L1,SMNR3012-470MT,C135236
0.1uF,C1,C_0603_1608Metric,C14663
0.1uF,"C15,C16,C17,C18,C19,C20,C23,C24",C_0402_1005Metric,C1525
27pF,"C11,C12",C_0402_1005Metric,C1557
30pF,"C5,C6,C7",C_0402_1005Metric,C1570
1uF,"C3,C8,C9",C_0603_1608Metric,C15849
RP2040,U2,QFN-56-1EP_7x7mm_P0.4mm_EP3.2x3.2mm,C2040
LED_Small,D3,LED_0603_1608Metric,C2286
LED_Small,D2,LED_0603_1608Metric,C2290
27,"R10,R11",R_0402_1005Metric,C25156
10k,"R13,R8",R_0603_1608Metric,C25804
5.1k,"R5,R6",R_0402_1005Metric,C25905
USB_C_Receptacle_USB2.0_16P,"J4,J6",USB_C_Receptacle_HRO_TYPE-C-31-M-12,C2927038
W25Q64JVXGIQ TR,U3,DFN_XGIQ TR_WIN,C2940195
1uF,"C13,C14,C21,C22",C_0402_1005Metric,C52923
DRV8316CRRGFR,U1,VQFN40_RGF_TEX-L,C5447274
22uF,C10,C_0603_1608Metric,C59461
LED_Small,D1,LED_0603_1608Metric,C72038
47nF,C4,C_0402_1005Metric,C77012
12Mhz,Y1,Crystal_SMD_3225-4Pin_3.2x2.5mm,C9002
10uF,C2,C_0603_1608Metric,C96446
Conn_01x03,J2,ESC,
